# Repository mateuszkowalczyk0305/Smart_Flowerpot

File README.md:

# Smart Flowerpot - Projekt:

## 📝 Założenia projektowe:
- Wyświetlanie temperatury otoczenia na dołączonym wyświetlaczu
- Wyświetlanie natężenia światła na dołączonym wyświetlaczu
- Wyświetlanie wilgotności gleby na dołączonym wyświetlaczu, z dodatkową
informacją o aktualnym stanie nawodnienia kwiatka, dostępne możliwości to:
“Podlej”, “Podlana” i “Przelana”
- Automatyczna regulacja oświetlenia dołączonego do doniczki na podstawie
odczytu z czujnika natężenia światła, zapewnia to stałe i optymalne warunki
do rozwoju rośliny niezależnie od pory dnia i warunków pogodowych.
- Do przetwarzania danych z czujników i wyświetlania ich na dołączonym
wyświetlaczu LCD wykorzystany zostanie mikrokontroler Arduino Uno R3,
natomiast kod odpowiedzialny za procedure tego przetwarzania napisany
zostanie w środowisku Arduino IDE.
- Do sterowania oświetleniem wykorzystany zostanie zaprojektowany przez nas
układ analogowy generujący sygnał PWM ze zmiennym wypełnieniem
zależnym od odczytu z czujnika natężenia światła(fotorezystorem)
- Wybór obudowy zapewniającej schludny, stosunkowo innowacyjny oraz
minimalistyczny wygląd

## 💡 Schemat pogladowy działania:

### ➖ Sterownik paska LED 'Smart_Flowerpot/LTspice':
Do zaprojektowania analogowej części układu wykorzystano program LTspice 
, Jest to część układu odpowiedzialna za generowanie sygnału PWM o
zmiennym wypełnieniu, a tym samym sterująca oświetleniem doniczki.

#### Szczegółowy opis układu:
Głównym elementem powyższego układu analogowego jest układ scalony
NE555(Rys.3). Odpowiada on za generację sygnału PWM, układ ten może
pracować w trybie monostabilnym, bądź astabilnym. W naszym projekcie
wykorzystujemy tryb astabilny w celu generacji ciągłego sygnału prostokątnego.
Rezystory R1, R2 odpowiadają za określenie częstotliwości generowanego
sygnału.
Kondensator C1 służy jako kondensator bocznikowy i zapewnia zasilanie o
niskiej impedancji, stabilizuje również działanie generatora PWM.
Wzmacniacz operacyjny TL081 pełni rolę komparatora, porównując napięcie
odniesienia z napięciem z dzielnika napięcia(w rzeczywistej wersji z napięciem z
mikrokontrolera Arduino Uno R3).
Tranzystor MOSFET IRF740 pod wpływem generowanego sygnału PWM
włącza się i wyłącza sterując diodą LED w sposób umożliwiający manipulację
natężeniem świecenia tych diod.
Pasek diod LED SMD5050 12V IP65 emituje światło o natężeniu zależnym od
współczynnika wypełnienia PWM, jej zasilanie kontrolowane jest przez tranzystor.
Źródło zasilania V1 dostarcza napięcie zasilania o wartości 5V do układu, jest
to napięcie podawane przez mikrokontroler.
Kondensator C2 oraz rezystor R3 filtrują napięcie odniesienia komparatora.
Rezystor R6 ogranicza prąd płynący przez pasek diod LED, chroniąc je tym
samym przed przepięciami.
Źródło zasilania V2 ma wartość 9V i dostarcza napięcie do obwodu diod LED.

#### Symulacja w programie LTspice:
Przeprowadzono symulacje działania, wcześniej omawianego układu
zaprojektowanego w programie LTspice. Podczas symulacji zbadano
napięcie zasilania obwodu diod(V(n001)), sygnał PWM podawany na bramkę
tranzystora(V(n005)) oraz prąd indukowany na diodach LED(I(D1)). Z
wykorzystaniem kursorów ustalono, że napięcie na bramce od którego prąd zaczyna
przepływać przez diody wynosi 1.72V, jest to wartość Vth(Gate Threshold Voltage)
poniżej zakresu podanego przez producenta, jednak należy wziąć pod uwagę, że
warunki dla których te zakresy zostały podane znacznie odbiegają od warunków w
zaprojektowanym, na potrzeby tego projektu układzie.

### ➖ Eagle:

#### Schemat układu:
Następnym krokiem po zaprojektowaniu układu i jego symulacji w programie
LTspice było wykonanie schematu płytki PCB w programie Eagle. W pierwszej
kolejności należało wykonać schemat układu w sposób podobny do wykonanego
uprzednio w LTspice, z tą różnicą, że schemat w programie Eagle uwzględnia
wszystkie bloki układu, jak i wymaga dobrania złączy kołkowych, listw zaciskowych,
bądź innego elementu umożliwiającego podłączenie zasilania. Na schemacie
można wyróżnić dwa bloki zasilające, główny obwód NE555 oraz wzmacniacza
wykorzystywanego jako komparator i obwód paska diod LED z tranzystorem
pełniącym rolę klucza między obwodem głównym, a obwodem diod LED.

#### Projekt PCB:
Następnie wykonano projekt płytki obwodu drukowanego z topologią
połączeń, wszystkie ścieżki poprowadzono w warstwie dolnej, przy
projektowaniu stosowano się do zasad zamieszczonych w dołączonym pliku
“OpenLab.dru”. Popełniono błąd przy dobieraniu wielkości pól lutowniczych, jednak
po wytrawieniu płytki udało się zrealizować w pełni działający układ. Topologia
połączeń została przemyślana i kilkukrotnie była optymalizowana, tak aby spełniała
kryteria i jednocześnie była uproszczona w jak największym stopniu. Zastosowano
trzy listwy zaciskowe - anody znajdują się po prawej stronie, natomiast katody po
lewej.

### ➖ Wykaz elementów:
Elementy wykorzystane do przygotowania płytki drukowanej:
- NE555
- Rezystory:
1. 2x 10kΩ
2. 1x 100Ω
3. 2x 1kΩ
- Kondensatory:
1. ceramiczny 100nF
2. elektrolityczny 1μF
- Wzmacniacz operacyjny TL081
- Tranzystor polowy IRF740
Poza elementami niezbędnymi do przygotowania płytki drukowanej
generującej sygnał PWM, w projekcie wykorzystano:
- Czujniki:
1. czujnik temperatury DS18B20 - cyfrowy czujnik temperaturowy z
interfejsem one-wire
2. czujnik wilgotności gleby firmy OEM - analogowy czujnik
składający się z sondy pomiarowej i modułu detektora
3. fotorezystor 10kΩ - pełniący role czujnika naświetlenia
- Arduino UNO R3 jako serce całego układu
- Wyświetlacz LCD
- Pasek LED SMD5050 12V IP65 pełniący rolę źródła światła
- Rezystory: x2 1[kΩ], x1 100 [Ω], x1 10 [kΩ]
- Kondensatory: x1 100 [nF], x1 1 [uF]
- Doniczka Agate 23 cm czarna VERDENIA
- Tranzystor IRF740
Całość układu jest zasilana bateryjne z 6 baterii umieszczonych w koszyku

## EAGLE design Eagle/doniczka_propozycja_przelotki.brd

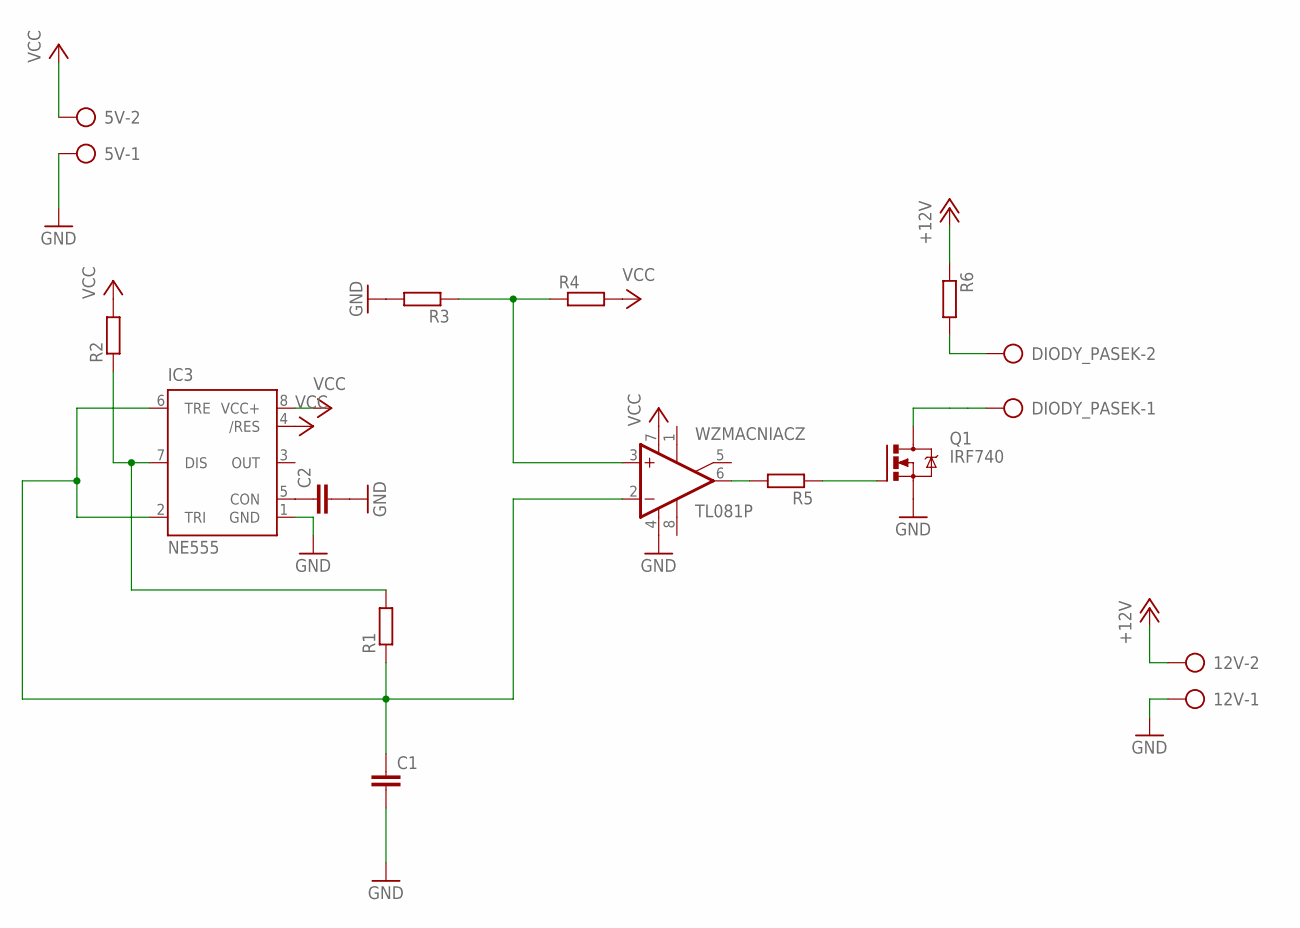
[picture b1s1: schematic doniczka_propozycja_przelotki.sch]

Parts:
5V, 12V: AK500/2
C1, C2: C-EU025-024X044; C025-024X044
DIODY_PASEK: AK500/2
IC3: NE555; DIL-08
Q1: IRF740; TO220BV
R1, R2, R3, R4, R5, R6: R0204/7; 0204/7
WZMACNIACZ: TL081P; DIL08

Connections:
+12V: 12V.2, R6.1
GND: 5V.1, 12V.1, C1.2, C2.2, IC3.1 (GND), Q1.S, R3.2, WZMACNIACZ.4 (V-)
unnamed: R3.1, R4.1, WZMACNIACZ.3 (+IN)
unnamed: IC3.7 (DIS), R1.2, R2.1
unnamed: C2.1, IC3.5 (CON)
unnamed: C1.1, IC3.2 (TRI), IC3.6 (TRE), R1.1
unnamed: R5.2, WZMACNIACZ.6 (OUT)
unnamed: Q1.G, R5.1
unnamed: DIODY_PASEK.2, R6.2
unnamed: DIODY_PASEK.1, Q1.D
VCC: 5V.2, IC3.4 (/RES), IC3.8 (VCC+), R2.2, R4.2, WZMACNIACZ.7 (V+)

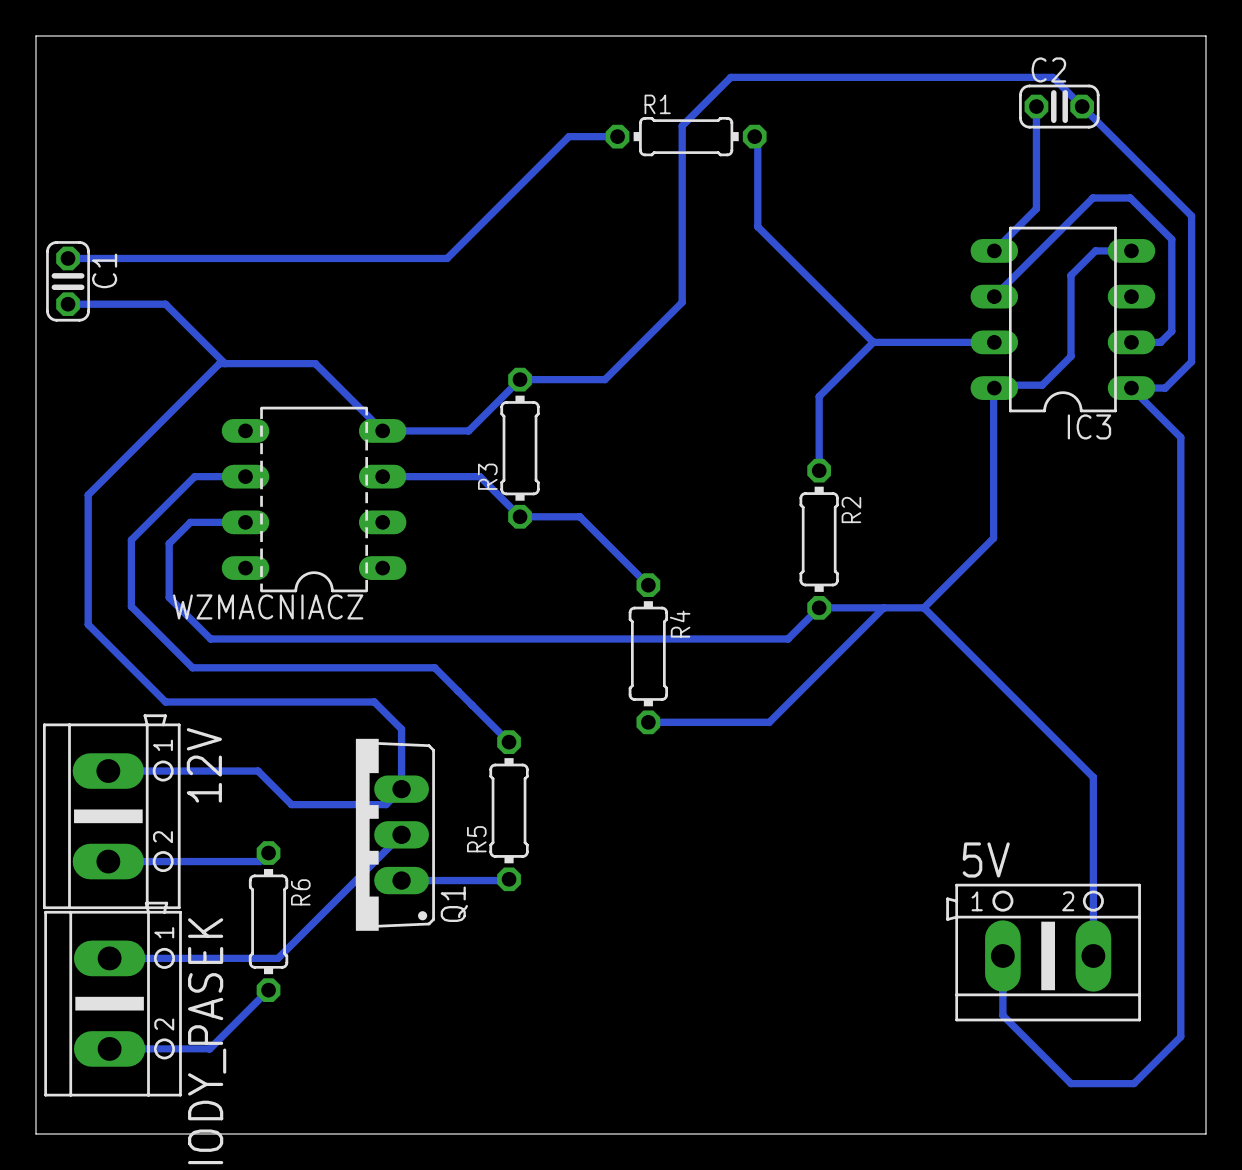
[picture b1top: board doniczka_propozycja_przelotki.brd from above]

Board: 2 copper layers, 65.0 x 61.0 mm, 14 parts (0 on the bottom side), 11 nets.

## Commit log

2024-03-28 LTspice PWM
2024-03-28 schemat
2024-04-10 eagle update
2024-04-19 update - eagle PCB ostatecza wersja
2024-05-08 zakończenie cz. elektronicznej.
    Podłączenie na płytce stykowym pierwszych czujników + zamknięcie części sterownika do paska LED.
2024-06-10 last_sommit
2024-06-11 commit_last
2024-06-11 README update
2024-06-11 czystki
2024-06-11 Raport czyszczenie
